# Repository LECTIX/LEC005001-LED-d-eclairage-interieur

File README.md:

# LEC005001 - LED d’éclairage intérieur
Fichiers sources pour le produit LEC005001

## Description du produit

Éclairez un batiment ou une partie d'un batiment à l'aide de ce petit circuit possédant led et résistances.
- **BLANC** ton froid
- **ALIMENTATION** 5 à 16 V DC
- **RÉSISTANCE** de 500 ohm intégrée
- **PRATIQUE** s’intégre facilement dans les maquettes
- **FIXATION** avec vis ou ruban double face

## Applications

- Éclairage intérieur complet d’un petit batiment.
- Éclairage d’une pièce spécifique d’un batiment.

## Installation

L’installation est simple et rapide :

1.Souder des fils sur les bornes + et -.
1.Installer la led dans la maquette à éclairer à l’aide de petites vis ou de ruban double face.
1.Faire ressortir les fils de la maquette.
1.Brancher sur une alimentation de moins de 16 V DC.
1.Profitez d’une nouvelle dimension dans l’éclairage des batiments de votre réseau.

## Utiliser les fichiers sources pour fabriquer le produit

Il n'est **pas nécessaire de savoir souder ou d'être bon en électronique** pour se procurer ce produit. Grâce aux fichiers sources publiés ici, vous pouvez être en mesure de faire fabriquer ce produit par un sous traitant.

### Faire fabriquer chez un sous traitant

Il est aujourd'hui possible de faire fabriquer à moindre cout des cartes électroniques. Nous recommendons [JLCPCB](https://jlcpcb.com/) si vous voulez aller au moins cher. Si vous préférez un acteur européen, [eurocircuits](https://www.eurocircuits.com/) est un des acteurs reconnus.

1. Télécherger les sources de ce produit en cliquant sur le bouton `Code`, puis `Download ZIP`.
1. Décompresser le dossier.
1. Les fichiers pour la fabrication se trouvent dans le répertoire `hardware/prod`.
1. Se connecter sur [https://cart.jlcpcb.com/quote](https://cart.jlcpcb.com/quote)
1. Cliquer sur le bouton `Add gerber file` et sélectionner le fichier `gerbers.zip`.
1. Sélectionnez la quantité de cartes que vous souhaitez dans le champs `PCB Qty`.
1. Laisser toutes les autres options par défaut, puis cliquez sur le toggle switch en face de `PCB Assembly`, et enfin sur le bouton `confirm`.
1. Une preview de la carte électronique sans les composants doit apparaitre. Cliquez sur `NEXT`.
1. Cliquez sur le bouton `Add BOM File`, puis sélectionnez le fichier `bom.csv`
1. Cliquez sur le bouton `Add CPL File`, puis sélectionnez le fichier `pos.csv`
1. **Vérifier que tous les composants sont en stock** et bien sélectionnés, puis cliquez sur `NEXT`.
1. Une preview de la carte avec ses composants apparait. Continuer le chemin en cliquant sur `NEXT`.
1. Le prix final apparait. Sélectionnez la catégorie du produit, puis cliquez sur `SAVE TO CART`.
1. Une fois sauvegardé dans votre panier, vous pouvez valider votre commande et choisir le moyen d'acheminement. Afin de ne pas avoir à se préoccuper des frais de douane, nous vous conseillons de choisir une méthode d'expédition DDP.

Vous receverez vos cartes sous 1 à 3 semaines. 

**Nous ne sommes en aucun cas responsables des cartes qui arriveraient défectueuses ou non fonctionnelles.**

### Modifications des fichiers sources

Installez kicad 6 (ou version supérieure), et ouvrez le fichier LEC005001.kicad_pro

### Regénérer les fichiers gerber, BOM, et position (Optionnel)

Peut se faire simplement en utilisant kikit :

```
cd hardware

# generate PCB panel (panel config can be change in panel-config.json)
docker run --rm -w /kikit -v $PWD:/kikit yaqwsx/kikit kikit panelize -p panel-config.json LEC005001.kicad_pcb LEC005001-panel.kicad_pcb

# generate assembly files
docker run --rm -w /kikit -v $PWD:/kikit yaqwsx/kikit kikit fab jlcpcb --assembly --no-drc --schematic LEC005001.kicad_sch --field LCSC --corrections JLCPCB_CORRECTION --nametemplate LEC005001_{} LEC005001-panel.kicad_pcb prod/

```

## License
Tous nos fichiers sont plubliés sous la license CERN Open Hardware Licence Version 2 - Strongly Reciprocal

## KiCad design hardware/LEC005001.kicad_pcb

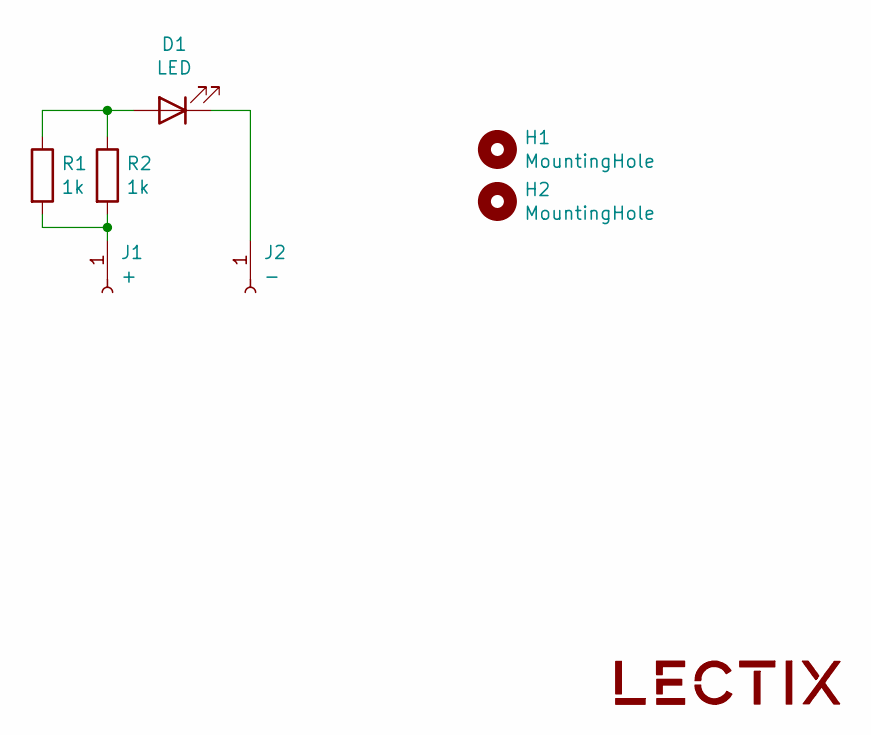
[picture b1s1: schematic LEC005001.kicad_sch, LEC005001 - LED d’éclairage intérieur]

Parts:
D1: LED; LED_0603_1608Metric; LCSC C2290
H1, H2: MountingHole; MountingHole_3.2mm_M3
J1: +; TestPoint_Pad_2.0x2.0mm
J2: -; TestPoint_Pad_D2.0mm
LOGO1: logo_lectix_25mm; Logo_10mm
R1, R2: 1k; R_0805_2012Metric; LCSC C17513

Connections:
unnamed: D1.1 (K), J2.1
unnamed: D1.2 (A), R1.1, R2.1
unnamed: J1.1, R1.2, R2.2

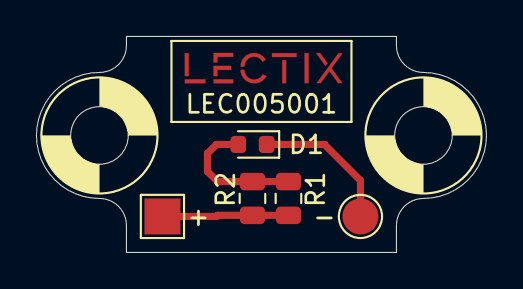
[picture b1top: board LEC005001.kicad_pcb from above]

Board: 2 copper layers, 25.0 x 12.0 mm, 8 parts (0 on the bottom side), 3 nets.

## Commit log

2023-04-16 Add kicad source files + gerbers
2023-04-16 Add panel prod file
